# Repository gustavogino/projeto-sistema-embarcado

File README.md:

# Projeto de Sistemas Embarcados (Apenas para aprendizagem)

Este projeto foi desenvolvido para aprender a criar um produto do zero, desde-o levantamento de requisitos, passando pelo diagrama de blocos, elaboração do esquema elétrico, criação da PCB de 2 layers (Placa de Circuito Impresso de duas camadas), o desenvolvimento do firmware do produto e por fim a documentação completa do projeto.

Esquema Elétrico:

PCB lado TOP:
.png?raw=true)

PCB lado Bottom:
.png?raw=true)

Os códigos fontes para verificação e alteração podem ser acessados nas suas respectivas pastas.

ATENÇÃO: Este projeto não foi fabricado de fato, apenas foi realizado para aprendizagem, não replique este produto para fins médicos, nenhuma garantia de funcionamento é fornecida. Utilize-o por sua conta e risco.

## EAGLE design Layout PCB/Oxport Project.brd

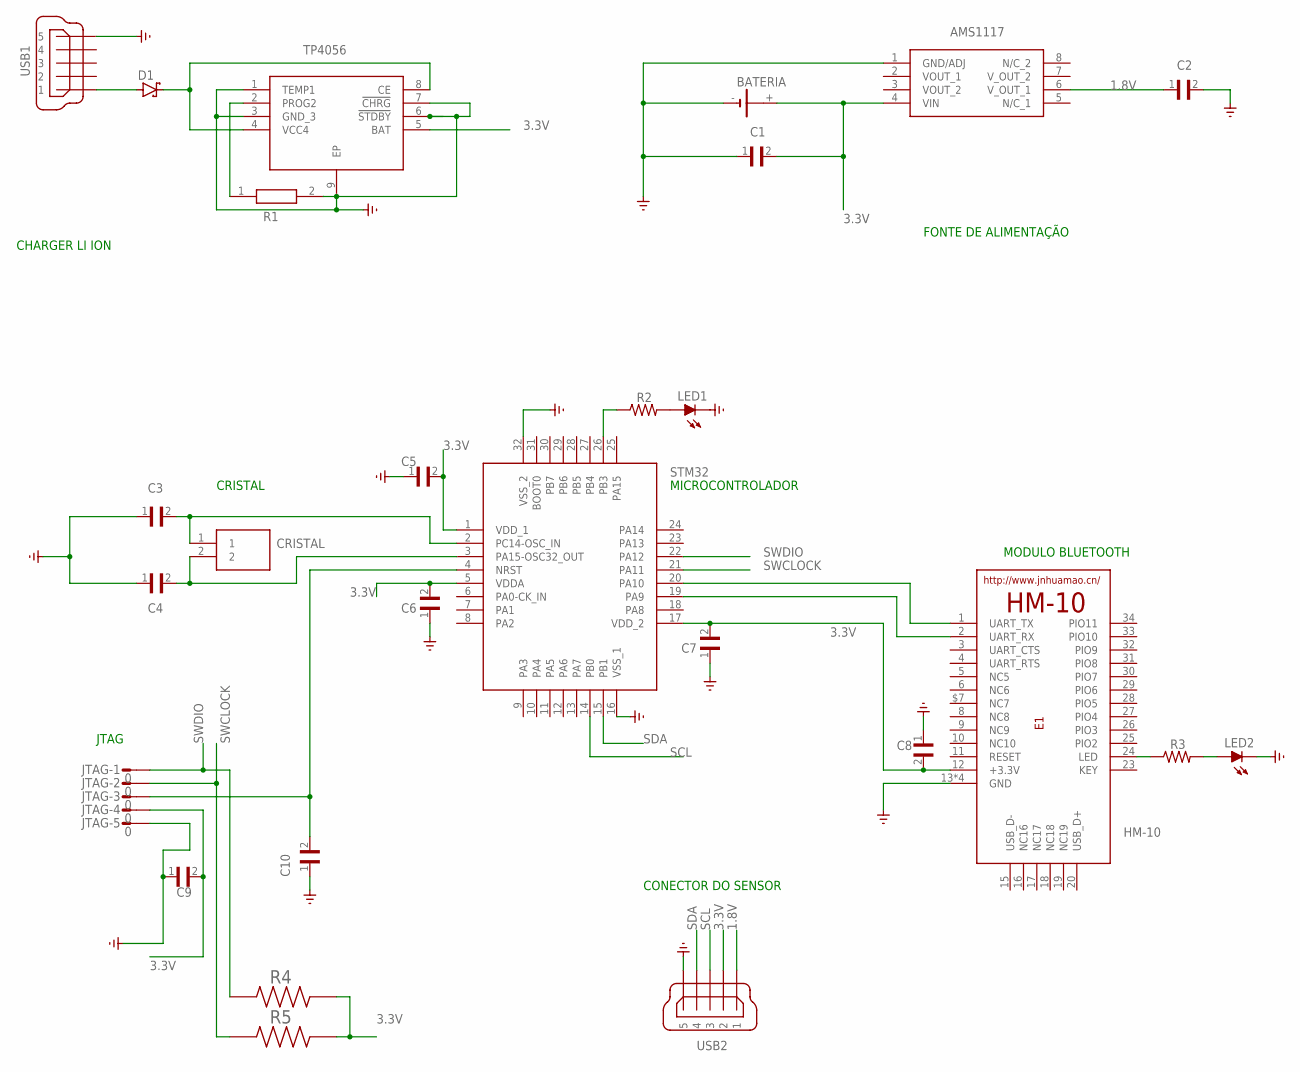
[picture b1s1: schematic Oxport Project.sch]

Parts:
3.3V: STM32L031K6T6TR; QFP80P900X900X160-32N
BATERIA: CR1/2
C1, C2, C5, C6, C7, C8, C9, C10: VJ0603Y104KLXAC5G; CAPC1608X92N
C3, C4: GRM1885C2A4R3CZ01D; CAPC1608X90N
CRISTAL: NX3215SA-32.768K-EXS00A-MU0000; NX3215SA32768KEXS00AMU00003
D1: BAT60J; SOD323_ST
E1: HM-10-BOARD; 26.9X13X2.2_BOARD
IC2: AMS1117CS-1.8; SOIC127P599X175-8N
J1: TP4056; SOIC127P600X175-9N
JTAG: 0; L05P
LED1, LED2: 1; LED_CHIP-LED0603MP
MINI_USB: MINI-USB_SHIELD5P4-32005-501; 32005-501
R1: CRCW08051K00FKEB; RESC2012X50N
R2, R3: 1623232-1; RESC2012X65N
R4, R5: CRGCQ1206J10K; RESC3115X65N
USB1: MINI-USB_SHIELD5P4-32005-501; 32005-501

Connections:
1.8V: C2.1, IC2.6 (V_OUT_1), USB1.1
3.3V: 3.3V.1 (VDD_1), 3.3V.5 (VDDA), 3.3V.17 (VDD_2), BATERIA.+, C1.2, C5.2, C6.2, C7.2, C8.2, C9.2, E1.12 (+3.3V), IC2.4 (VIN), J1.5 (BAT), JTAG.4, R4.2, R5.2, USB1.2
GND: 3.3V.16 (VSS_1), 3.3V.32 (VSS_2), BATERIA.-, C1.1, C2.2, C3.1, C4.1, C5.1, C6.1, C7.1, C8.1, C9.1, C10.1, E1.13 (GND), E1.14 (GND), E1.21 (GND), E1.22 (GND), IC2.1 (GND/ADJ), J1.1 (TEMP1), J1.3 (GND_3), J1.6 (!STDBY), J1.7 (!CHRG), J1.9 (EP), JTAG.5, LED1.C, LED2.C, MINI_USB.5, R1.2, USB1.5
unnamed: D1.A, MINI_USB.1
unnamed: 3.3V.2 (PC14-OSC_IN), C3.2, CRISTAL.1
unnamed: 3.3V.3 (PA15-OSC32_OUT), C4.2, CRISTAL.2
unnamed: 3.3V.20 (PA10), E1.1 (UART_TX)
unnamed: 3.3V.19 (PA9), E1.2 (UART_RX)
unnamed: 3.3V.26 (PB3), R2.1
unnamed: E1.24 (LED), R3.1
unnamed: LED2.A, R3.2
unnamed: LED1.A, R2.2
unnamed: D1.C, J1.4 (VCC4), J1.8 (CE)
unnamed: J1.2 (PROG2), R1.1
RESET: 3.3V.4 (NRST), C10.2, JTAG.3
SCL: 3.3V.14 (PB0), USB1.3
SDA: 3.3V.15 (PB1), USB1.4
SWCLOCK: 3.3V.21 (PA11), JTAG.2, R5.1
SWDIO: 3.3V.22 (PA12), JTAG.1, R4.1

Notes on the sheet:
CHARGER LI ION
FONTE DE ALIMENTAÇÃO
MICROCONTROLADOR
MODULO BLUETOOTH
JTAG
CRISTAL
CONECTOR DO SENSOR
USB1
USB2
STM32
HM-10
AMS1117

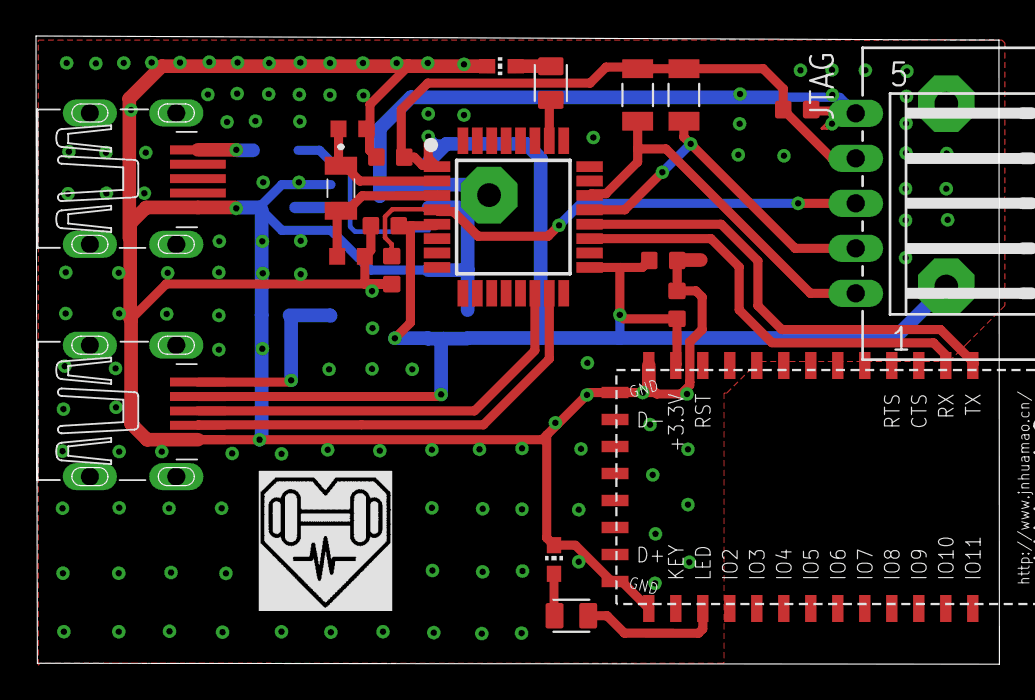
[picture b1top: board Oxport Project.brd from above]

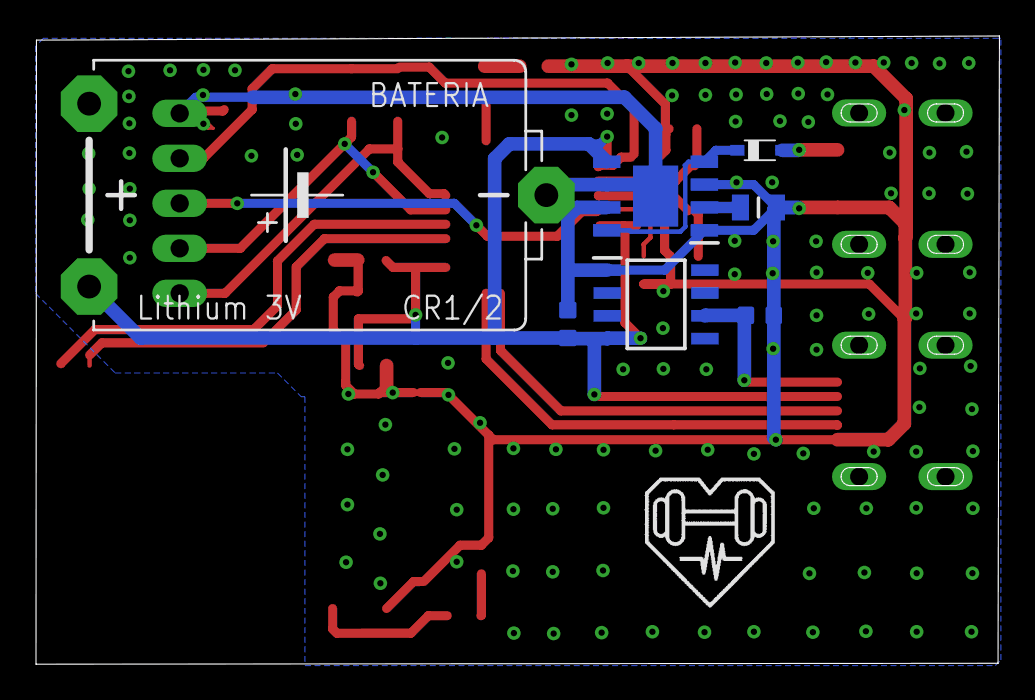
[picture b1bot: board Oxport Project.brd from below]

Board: 2 copper layers, 53.5 x 34.9 mm, 27 parts (7 on the bottom side), 19 nets.

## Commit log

2021-06-28 Upload
